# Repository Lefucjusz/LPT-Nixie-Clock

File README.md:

# LPT-Nixie-Clock
DOS-controlled Nixie clock, built with four IN-1/LC-516 tubes and interfaced through the LPT port.

<figure>
    
    <figcaption><i>Photo of a complete project (LC-516 tubes)</i></figcaption>
</figure>

## Features
* Supports IN-1 and LC-516 Nixie tubes
* Multiplexed display with four digits and a colon
* Onboard high-voltage boost converter; requires only a single 12V power supply
* Serial control interface using just three control wires
* Hardware designed exclusively with easily available components
* Control software implemented as a DOS TSR written in TASM
* Uses the AT-style RTC programming model as the time source and multiplexing timebase
* Connection via the PC’s LPT port

## Motivation
This project is another attempt to answer a question I’ve been asking myself ever since I built the [Xi8088](https://github.com/skiselev/xi_8088):

*What can I use this PC for that it was never really designed to do, yet is still possible, reasonably practical, and fun to work on?*

My first attempt was a WAV player - [WAVWSS](https://github.com/Lefucjusz/WAVWSS). With that working, I started looking for another challenge, Nixie clock felt like a perfect next step:

* it smoothly merges insanity with practicality: it is a Nixie clock - a useful and visually appealing device - controlled by genuinely ancient hardware that
was never intended for such a task, especially not via a printer port;
* while not fully period-correct, the combination of a PC/XT-class computer built largely from 74xx TTL logic and Nixie tubes has a strong appeal for a low-level
tinkerer like me :smile:;
* it provided a good opportunity to learn long-forgotten skills such as writing DOS TSRs, particularly in assembly language, the task I had never tried before.
The project is programmatically simple, making debugging relatively straightforward when things went wrong;
* it allowed me to validate the idea of a Nixie tube driver circuit built entirely from easily available components, avoiding long-discontinued parts such as
SN74141 or its Soviet counterpart K155ID1, which are increasingly expensive and slowly becoming unobtainium;
* finally, it gave me the motivation to put to use a set of IN-1 Nixie tubes I bought around 2020, but had never used due to their large, hard to use sockets.

## Hardware

> [!CAUTION]
> This project involves high voltages! Although the external power supply is only 12V, voltages of around 200V are present on the PCB and components during normal
operation. Even higher voltages may occur if the boost converter feedback loop malfunctions, for example due to incorrect PCB assembly. **Such voltages can be lethal.**
The author takes no responsibility for any damage, injury, or loss resulting from the use or construction of this project. Build and operate it entirely at your own risk.

> [!WARNING]
> Use of this project may pose a risk to your vintage hardware. The author accepts no responsibility for any resulting damage.
 
### Schematic and PCB layout

[Schematic](https://github.com/Lefucjusz/LPT-Nixie-Clock/blob/master/kicad/lpt_nixie_clock_schematic_color.pdf)

[PCB layout](https://github.com/Lefucjusz/LPT-Nixie-Clock/blob/master/kicad/lpt_nixie_clock_board_color.pdf)

### Principle of operation

#### Logic design and display interface
The logic section, which forms the input interface for the display, consists of U3 (4028), U6 (74HC595), and U7 (74HCT74). U6 together with U7 forms a 9-bit
SIPO register with an output latch. The register outputs are connected to:
* the anode drivers for the Nixie tubes;
* the colon cathode driver;
* the BCD-to-decimal decoder (U3), which controls the Nixie cathode drivers.

The display operates in a multiplexed fashion: all corresponding Nixie digits share connections, and only one tube is turned on at a time. Rapidly switching between
tubes (every 1/64 millisecond in this project) creates the illusion that all tubes are lit simultaneously. This approach drastically reduces the number of required shift
register outputs or control lines compared to static (individual) tube control.

The display control word is loaded serially using three lines: `DATA`, `CLOCK`, and `LATCH`. The loading occurs in two steps:
1. The control word is shifted into the register using the `DATA` and `CLOCK` lines.
2. After the word is fully loaded, a rising edge on the LATCH line updates the output register.

The exact timing diagram, along with a description of each control word bit, is shown below.

* `A1..4` - logic high enables the anode driver, A1 is the leftmost tube
* `1..8` - BCD value of a digit to be displayed
* `:` - logic high turns on the colon 

Some design choices may seem unusual at first. Initially, I did not use the 4028 decoder for the cathode control signals. Instead, the inputs of the Nixie cathode drivers
were connected directly to the outputs of two cascaded 74HC595 shift registers. The problem with this approach was efficiency: sending 15 bits
(10 cathodes, 4 anodes, colon) to a shift register is more costly than sending just 9 bits. Each bit requires 3 OUT instructions:
1. set `DATA` line state,
2. set `CLOCK` line high,
3. set `CLOCK` line low.

Each control word also requires a `LATCH` toggle to update output register: 2 additional OUT instructions.

At a 256Hz multiplexing rate, using a 15-bit register results in:

```
256 * ((15 * 3) + 2) = 12032 OUT instructions per second
```

Tests on a breadboard prototype showed that spamming the LPT port with this many instructions from within an ISR was beyond the capabilities of an 8088 at 4.77MHz.
Even at 8MHz, the PC was noticeably slowed - for example, WAV playback using WAVWSS would stutter while the clock was running.

Switching to a 9-bit register reduces the required instructions to:

```
256 * ((9 * 3) + 2) = 7424 OUT instructions per second
```

Still significant, but much more manageable.

With a 9-bit register, only one bit of a second, cascaded 74HC595 was actually needed. Rather than using an entire additional shift register just for a single bit,
I replaced it with a 74HCT74 flip-flop, which met the circuit requirements much better. I also happened to have plenty of 74x74 chips and only a few 74HC595s, so this
choice made it easy to make good use of the components I already had on hand.

#### Anode drivers
For the anode drivers, I usually go with the classic solution of a two-transistor high-side switch, which allows controlling high voltages using standard logic levels.

<figure>
    
    <figcaption><i>Two-transistor high side switch</i></figcaption>
</figure>

<br/>
<br/>

This time, however, I decided to experiment with an approach using optocouplers. I had seen similar solutions in other projects, but they typically used TLP627
optocouplers or alternatives with a similarly high collector-emitter breakdown voltage `VCEO ≈ 300V`. They are much harder to source than common, widely
available types.

I wondered whether such a high breakdown voltage was really necessary. After some consideration, I thought that as long as the following condition is met, the
circuit should operate correctly:

```
Va < Vm + VCEO

where: 
Va - anode voltage from boost converter
Vm - maintaining voltage of a Nixie tube
VCEO - collector-emitter breakdown voltage of an optocoupler’s transistor
```

Looking through my components, I found a few CNY17-3 optocouplers with `VCEO = 70V` and decided to test them in a prototype circuit. They worked, and also reduced
the component count compared to the traditional 2-transistor driver, so I decided to keep this solution.

#### Cathode drivers

Using the same reasoning as for the anode driver, I decided to experiment with ULN2004 chips for the Nixie cathode drivers. These have a VCEO of only 50V, so
this solution is definitely not very robust and is far from production-ready. The drivers operate close to or even slightly above their absolute maximum ratings.

During several months of testing, I didn’t blow a single ULN2004 channel, so either I was very lucky or happened to have particularly sturdy chips. However, the
ULN2004-based solution does cause an issue when driving the neon bulbs used for the colon; see [Known Issues](#known-issues).

> [!WARNING]
> If anyone comes across this project and wants to take inspiration from it, please avoid this approach in your own projects! Operating so close to the maximum 
ratings of components is an engineering antipattern that should be avoided whenever possible, even in non-critical applications.

#### Boost converter

The boost converter circuit is a classic NE555-based circuit, using the chip in a somewhat unconventional way. This design has a number of drawbacks: low efficiency,
feedback that affects not only the duty cycle but also the switching frequency, poor voltage stability under varying load, significant temperature drift due to the
reference being based on forward voltage of feedback transistor's B-E junction, etc.

Despite these limitations, I chose this approach for one main reason: it is simple and relies only on widely available components.

### Assembly

> [!WARNING]
> Nixie tubes and neon bulbs are mounted on the opposite side of the PCB from the rest of the components.

#### PCB - top side

The top side of the PCB contains all components except the Nixie tubes and neon bulbs. When assembling this layer, install the components from the smallest to the largest -
this makes the process much easier.

Pay close attention to the polarity of diodes and electrolytic capacitors, and ensure all ICs are installed with the correct orientation - `U4` and `U5` are oriented differently
from the rest. I strongly recommend using sockets for all ICs. I use them in all of my projects: they are inexpensive and can save a lot of soldering work if any IC ever
needs to be replaced.

#### PCB - bottom side
The bottom side of the PCB is where the Nixie tubes and neon bulbs are mounted. Start by installing the Nixie tubes. They can be either soldered directly to the PCB or
socketed. Both approaches have their advantages and drawbacks:
* direct soldering is quicker, but replacing a tube later will be difficult and will require desoldering;
* socketing makes tube replacement easy, but is more involved during assembly.

If you decide to solder the tubes directly, there is not much to watch out for - the tube base is keyed, so simply align it correctly, insert it into the PCB, and solder.

If you decide to use sockets, the process is a bit more complicated. Unfortunately, Nixie tube sockets were never standardized and are no longer manufactured, so they are
not available as off-the-shelf parts. For this design, I used female contacts intended for 5.08mm Molex-type CD/HDD power plugs. These are widely available and likely to
remain so for the foreseeable future.

However, these contacts cannot be used as-is - they require slight modification to fit the circular pads on the PCB. This is the most tedious part of the socketing process:
1. Remove the cable crimp section of the contact by cutting or breaking it off. Its irregular shape prevents the contact from fitting properly into the circular PCB pad.
2. Check the fit in the PCB pad. Some contacts have a slightly oversized diameter. If a contact does not fit easily, gently squeeze the soldering end with pliers to reduce
the diameter.

<figure>
    
    <figcaption><i>Molex contact with cable crimp section removed</i></figcaption>
</figure>

<br/>
<br/>

Perform these two steps on all contacts before proceeding, so that they are ready for installation.

Once all contacts are modified, install the first set onto the pins of a Nixie tube. Installing the contacts on the tube first and inserting the assembly as a whole makes
it much easier to keep the contacts properly aligned. After the entire set of contacts is placed on the tube, align it with the PCB footprint using the base key, then
carefully insert all contacts into their respective pads. This step requires some patience; tweezers are very helpful here.

Once all pins are fully inserted - ideally up to the retention springs - solder the contacts, remove the tube, and repeat the entire process for the remaining three Nixie tubes.

After all the contacts have been soldered, install the neon bulbs, then insert Nixie tubes into the sockets.

#### PCB - cleaning and final inspection

When the assembly is completed, clean the PCB thoroughly using isopropyl alcohol to remove any residual flux. Perform a careful final inspection: check for bad solder joints,
accidental solder bridges or any potential shorts. Make sure all ICs are correctly oriented and look for any obvious mistakes before powering up the board.

<figure>
    
    <figcaption><i>Fully assembled PCB - top view</i></figcaption>
</figure>

#### LPT cable

To connect the device to the PC, an LPT-to-board connector cable is required. The wiring diagram is shown below.

| DB-25 LPT pin    | PCB connector pin | Signal name |
|------------------|-------------------|-------------|
| 2                | 4                 | DATA        |
| 3                | 3                 | CLOCK       |
| 4                | 2                 | LATCH       |
| 18-25 (pick one) | 1                 | GND         |

On the PC side, a standard male DB-25 connector is used. On the board side, any 4-pin connector with a 2.54 mm pitch that fits the available space can be used. In my build, 
I chose a Molex KK-254 series connector, mainly because I already had suitable parts left over from another project. The connector may also be omitted entirely, with the cable 
soldered directly to the PCB.

The cable itself must contain at least four conductors. I used a generic Cat 5e Ethernet cable, taking one wire from each twisted pair for the signal and connecting the 
corresponding paired wire to ground. This arrangement helps reduce noise pickup on the control lines.

### Bring-up

After the PCB is assembled and cleaned, the device is ready to be powered up for the first time. If the board was assembled correctly, it should work without issues. During 
the initial power-up, the Nixie tube anode voltage must be set to 170V. This adjustment is performed only once.

> [!CAUTION]
> Reminder: high voltages (up to approx. 200V) are present on the PCB during this procedure. Neither the board nor any components should be touched while the device
is powered. Capacitor C4 may remain charged for several minutes after the power supply has been turned off. Do not touch the board or components immediately after
power-down; always verify that the high-voltage rail has discharged before handling the PCB.

1. Set the `RV1` potentiometer (labeled `170V Adj.`) to approximately its mid-position. This provides a safe starting point and helps ensure that the output voltage
will not exceed the target value.
2. Connect a voltmeter with a range of at least 200V to the `TP1` test point.
3. Connect a 9-12V power supply with a current rating of at least 0.5A to the `J1` connector, observing correct polarity. The circuit includes reverse-polarity
protection, but it will not operate if the supply is connected backwards. If available, a bench power supply with adjustable current limiting is strongly recommended. 
Set the current limit to 0.5A.
4. Do not connect the control cable at this stage.
5. Turn on the power supply. Some digits may begin to glow faintly - this is normal. Upon power-up, the output states of the SIPO register are undefined. Due to
limitations of the 74HC595 reset mechanism (it clears only the shift register, not the output register), implementing a power-on reset circuit that guarantees all
tubes are off would significantly increase circuit complexity. Since the display is not intended to operate without control signals, I've decided that this behavior
is acceptable.
6. Adjust `RV1` until the voltage at `TP1` reads 170V ±2V. Turning the potentiometer clockwise increases the voltage; turning it counterclockwise decreases it.
**If the voltage at `TP1` exceeds 250V and cannot be reduced using `RV1`, immediately turn off the power supply and verify the assembly of the boost converter's
feedback loop. Continued operation at this voltage may cause `C4` to fail catastrophically.**
7. Turn off the power supply.
8. Connect the control cable between the LPT port and the board.
9. Start the DOS TSR.
10. Turn the power supply back on. If the board and the cable were assembled correctly, the display should show the current RTC time, and the colon should blink once per second.

### Known issues

#### Colon not turning off completely
This issue is caused by the low VCEO rating of the ULN2004. Neon bulbs have a much lower maintaining voltage than Nixie tubes and as a result, the condition
described in the [Anode Drivers](#anode-drivers) is not met. This causes the ULN2004 output transistor to enter C-E breakdown. Although the transistor is not
damaged due to the limited current, it continues to conduct even when its base is not being driven.

I didn't notice this problem during prototyping stage, as the neon bulbs I initially used happened to work correctly under these conditions. They likely have 
an unusually high maintaining voltage.

This issue can be worked around in two ways:

1. **Add a parallel resistor across each neon bulb.** Solder the resistor directly to the pads of each bulb. A value of 470kΩ works well in most cases. This forms
a resistor divider with the neon bulb’s  current-limiting resistor and lowers the voltage across the bulb below its maintaining voltage, even while the driver
transistor is in breakdown.
2. **Lower the anode voltage** using `RV1` until both neon bulbs fully extinguish when turned off. This will also reduce the brightness of Nixie tubes, though.

#### Too large footprint for non-polar capacitors
Somehow, I ended up selecting a footprint with a 7.5mm pin pitch instead of 5mm, and didn’t notice it despite reviewing the project countless times before placing an
order for PCBs. As a result, typical 100nF ceramic disc capacitors are too narrow for the footprint, and their leads need to be bent to fit. I’ll likely fix this if
I ever order another batch of PCBs, and (assuming the corrected version works as expected) I’ll update the design files.

### Bill of Materials
| Component type | Reference          | Description                                 | Quantity | Possible sources and notes                                          |
|----------------|--------------------|---------------------------------------------|----------|---------------------------------------------------------------------|
| PCB            | -                  | LPT Nixie Clock PCB                         | 1        | Your favourite PCB manufacturer                                     |
| Capacitor      | C1, C6, C7, C9-C11 | 100nF ceramic                               | 6        | TME CC-100N                                                         |
| Capacitor      | C2                 | 2.2nF ceramic or polyester                  | 1        | TME R82EC1220DQ50J                                                  |
| Capacitor      | C3                 | 47pF 1kV ceramic                            | 1        | TME CCH-47P/1000V                                                   |
| Capacitor      | C4                 | 4.7μF 250V electrolytic                     | 1        | TME PF2E4R7MNN0812                                                  |
| Capacitor      | C5                 | 330μF electrolytic                          | 1        | TME PF1C331MNN0812                                                  |
| Capacitor      | C8                 | 10μF electrolytic                           | 1        | TME CE-10/50PHT-Y                                                   |
| Resistor       | R1                 | 56kΩ                                        | 1        | TME MBB02070C5602FCT00                                              |
| Resistor       | R2                 | 1kΩ                                         | 1        | TME MRS25000C1001FCT00                                              |
| Resistor       | R3                 | 10kΩ                                        | 1        | TME MRS25000C1002FCT00                                              |
| Resistor       | R4                 | 2.2kΩ                                       | 1        | TME MRS25000C2201FCT00                                              |
| Resistor       | R5                 | 330kΩ                                       | 1        | TME MBB02070C3303FCT00                                              |
| Resistor       | R6                 | 820Ω                                        | 1        | TME MBB02070C8200FCT00                                              |
| Resistor       | R7, R9, R13, R15   | 470Ω                                        | 4        | TME MF006JJ0471A50                                                  |
| Resistor       | R8, R10, R14, R16  | 6.8kΩ                                       | 4        | TME MFFU2FF6801A50                                                  |
| Resistor       | R11, R12           | 180kΩ                                       | 2        | TME MRS25000C1803FCT00                                              |
| Resistor       | R17                | 0Ω                                          | 1        | Note: used only in prototype, install a jumper                      |
| Trimpot        | RV1                | 2.2kΩ                                       | 1        | TME CA6V-2K2                                                        |
| Diode          | D1                 | UF4007                                      | 1        | TME UF4007-DC                                                       |
| Diode          | D2                 | 1N5817                                      | 1        | TME 1N5817-ST                                                       |
| Inductor       | L1                 | 100μH 1A                                    | 1        | TME RLB0914-101KL                                                   |
| Transistor     | Q1                 | BC547C                                      | 1        | TME BC547C-DIO                                                      |
| Transistor     | Q2                 | IRF740                                      | 1        | TME IRF740PBF-BE3                                                   |
| Optocoupler    | OK1-OK4            | CNY17-3                                     | 4        | TME CNY17-3X                                                        |
| IC             | U1                 | NE555                                       | 1        | TME NE555P                                                          |
| IC             | U2                 | 78L05                                       | 1        | TME AS78L05Z-E1                                                     |
| IC             | U3                 | 4028                                        | 1        | TME CD4028BE                                                        |
| IC             | U4, U5             | ULN2004A                                    | 2        | TME ULN2004A                                                        |
| IC             | U6                 | 74HC595                                     | 1        | TME 74HC595N-TT                                                     |
| IC             | U7                 | 74HCT74                                     | 1        | TME SN74HCT74N                                                      |
| IC socket      | U1                 | 8-pin 300mil DIP socket                     | 1        | TME 1-2199298-2; Note: optional                                     |
| IC socket      | U3-U6              | 16-pin 300mil DIP socket                    | 4        | TME ICVT-16P; Note: optional                                        |
| IC socket      | U7                 | 14-pin 300mil DIP socket                    | 1        | TME ICVT-14P; Note: optional                                        |
| Fuse           | F1                 | 500mA 250VAC 5x20mm slow-blow fuse          | 1        | TME UDA500MA250V                                                    |
| Fuse socket    | F1                 | Fuse mounting contact                       | 2        | TME ZH8                                                             |
| Connector      | J1                 | 2-pin 5mm 90° screw terminal block          | 1        | TME DG301-5.0-2P12                                                  |
| Connector      | J2                 | Molex KK-254 4-pin PCB connector            | 1        | TME MX-6410-04A                                                     |
| Neon bulb      | NE1, NE2           | Neon bulb w/o resistor                      | 2        | TME NEON-2                                                          |
| Nixie tube     | V1-V4              | IN-1 or LC-516                              | 4        | eBay, Allegro etc.                                                  |
| Contact        | V1-V4              | CD/HDD 5.08mm female power plug contact     | 44       | TME DFC01DR; Note: 11 pcs. for each tube; optional, but recommended |
| Plug           | -                  | DB-25 male plug for cable                   | 1        | TME DSC-025; Note: for signal cable                                 |
| Plug enclosure | -                  | DB-25 plug enclosure                        | 1        | TME DSC-225; Note: for signal cable                                 |
| Plug           | -                  | Molex KK-254 4-pin cable connector          | 1        | TME MX-47054-1000; Note: for signal cable                           |
| Contact        | -                  | Molex KK-254 contact                        | 4        | TME MX-4809C-P914L; Note: for signal cable                          |
| Cable          | -                  | Any signal cable with at least 4 conductors | 1        | Note: for signal cable                                              |
| Power supply   | -                  | 9-12VDC 0.5A power supply                   | 1        | TME POSC12100A-25                                                   |

## Software
The program was developed on the Xi8088 using Borland Turbo Assembler 2.01. Initially, I considered implementing it in C, as this is my mother tongue in programming :smile:.
However, I decided it would be more interesting to go fully low-level, try 8088 assembly, and minimize the size of the TSR as much as possible.

To keep the design simple, I did not implement any unloading or presence-checking mechanisms. I also didn't explore loading the program into upper memory. My Xi8088 build has
only 640KB of RAM, so I neither had a practical need for this nor a convenient way to test it. The final TSR occupies 720B of conventional memory.

<figure>
    
    <figcaption><i>TSR memory usage</i></figcaption>
</figure>

### Principle of operation
At a high level, the program’s functionality is straightforward. Upon startup, it installs an interrupt handler for the RTC interrupt, configures the RTC interrupts and
terminates. From that point on, the RTC periodically invokes the installed handler, which is responsible for updating the display.

Internally, the program follows a fairly standard DOS TSR architecture and can be logically divided into an initialization part and a resident part. The initialization part runs
when the program is executed and is responsible for the following tasks:
* installing an interrupt handler for INT 70h (IRQ 8, connected to the RTC interrupt line), which effectively drives the entire resident part of the program;
* configuring the RTC periodic interrupt rate to 256Hz, which is used as the display multiplexing timebase;
* enabling the RTC update-ended interrupt, used to update the colon state and time variables;
* unmasking IRQ 8 in the 8259 PIC;
* terminating the program in a way that leaves the resident portion in memory.

The resident part is the core of the program. Each time the RTC asserts an interrupt request, the installed ISR is invoked and executes the following steps:
* all registers clobbered by the ISR are pushed onto the stack;
* the RTC interrupt flags are read to determine the interrupt source;
* if a periodic interrupt is pending, the display update procedure is executed; this procedure keeps track of the currently active Nixie tube to perform multiplexing, converts
the time variables into the serial control word format, transmits the data frame via the LPT port, and executes the cathode depoisoning algorithm (described below);
* if an update-ended interrupt is pending, the time update procedure is called; this procedure keeps the time variables and colon state synchronized with the RTC;
* finally, IRQ 8 is acknowledged in the 8259 PICs, register values are restored from the stack, and the ISR returns.

#### Cathode depoisoning algorithm
The purpose of this algorithm is to prevent (or at least reduce) a well-known phenomenon inherent to Nixie tube technology. When a cathode (digit) is active, material from
that cathode is sputtered onto the glass envelope and onto the inactive cathodes. If certain digits remain unused for long periods while others are displayed frequently, the
deposited material can become thick enough to disturb the current flow, causing so-called cathode poisoning. A poisoned cathode may glow very weakly, develop dark spots or
stop glowing altogether. Some excellent photographs illustrating this phenomenon can be found on [Dieter's Nixie World page](https://www.tube-tester.com/sites/nixie/different/cathode%20poisoning/cathode-poisoning.htm).

Some Nixie tubes are more prone to this than others, but over time the effect can show up in almost any tube if it is not actively prevented.

To counter this, a simple cathode “depoisoning” algorithm is implemented in the TSR. Once per hour, the algorithm cycles through all digits on all tubes, ensuring that every
cathode is periodically activated. This is a standard approach and one I have used in my Nixie-related projects from the beginning. It has proven very effective for IN-12 and
LC-531 tubes. I haven't had a long-term experience with IN-1 tubes yet, but I expect it to work just as well - time will tell :smile:.

<figure>
  
  <figcaption><i>Depoisoning algorithm at work (IN-1 tubes)</i></figcaption>
</figure>

### Compatibility
The software has not been tested on a wide range of machines, but it should work on any system with:
* an LPT port located at I/O address 378h and,
* an AT-style RTC using the MC146818P / DS1287 programming model.

In addition to the Xi8088 used for development, the program has been tested on a 386-class PC, where it worked without issues.

In principle, the software could be adapted to systems without such an RTC. The display update routine needs to be invoked at a rate of at least 250Hz to maintain smooth
multiplexing and an alternative time source would need to be provided.

The TSR uses the RTC interrupt exclusively; the original ISR previously installed on the RTC vector is replaced rather than chained. This is probably not the wisest design choice,
but as far as I am aware, DOS itself doesn't use this interrupt for any purpose. Problems may arise if other software expects to receive RTC interrupts.
Unfortunately, I don't know which programs might rely on this, as my retrocomputing experience is still fairly limited.

### Compiling
Assuming Borland Turbo Assembler 2.01 is installed and added to system PATH, the program can be assembled as follows.

1. Assemble the source file `CLOCK.ASM` using `TASM`:
```
tasm clock.asm
```
This will produce the object file `CLOCK.OBJ`.

2. Link the object file using `TLINK`:
```
tlink /t clock.obj
```
The `/t` switch tells the linker to use the tiny memory model and generate a `.COM` file instead of an `.EXE`.

If both commands run without errors, the output `CLOCK.COM` file will be created and is ready to run.

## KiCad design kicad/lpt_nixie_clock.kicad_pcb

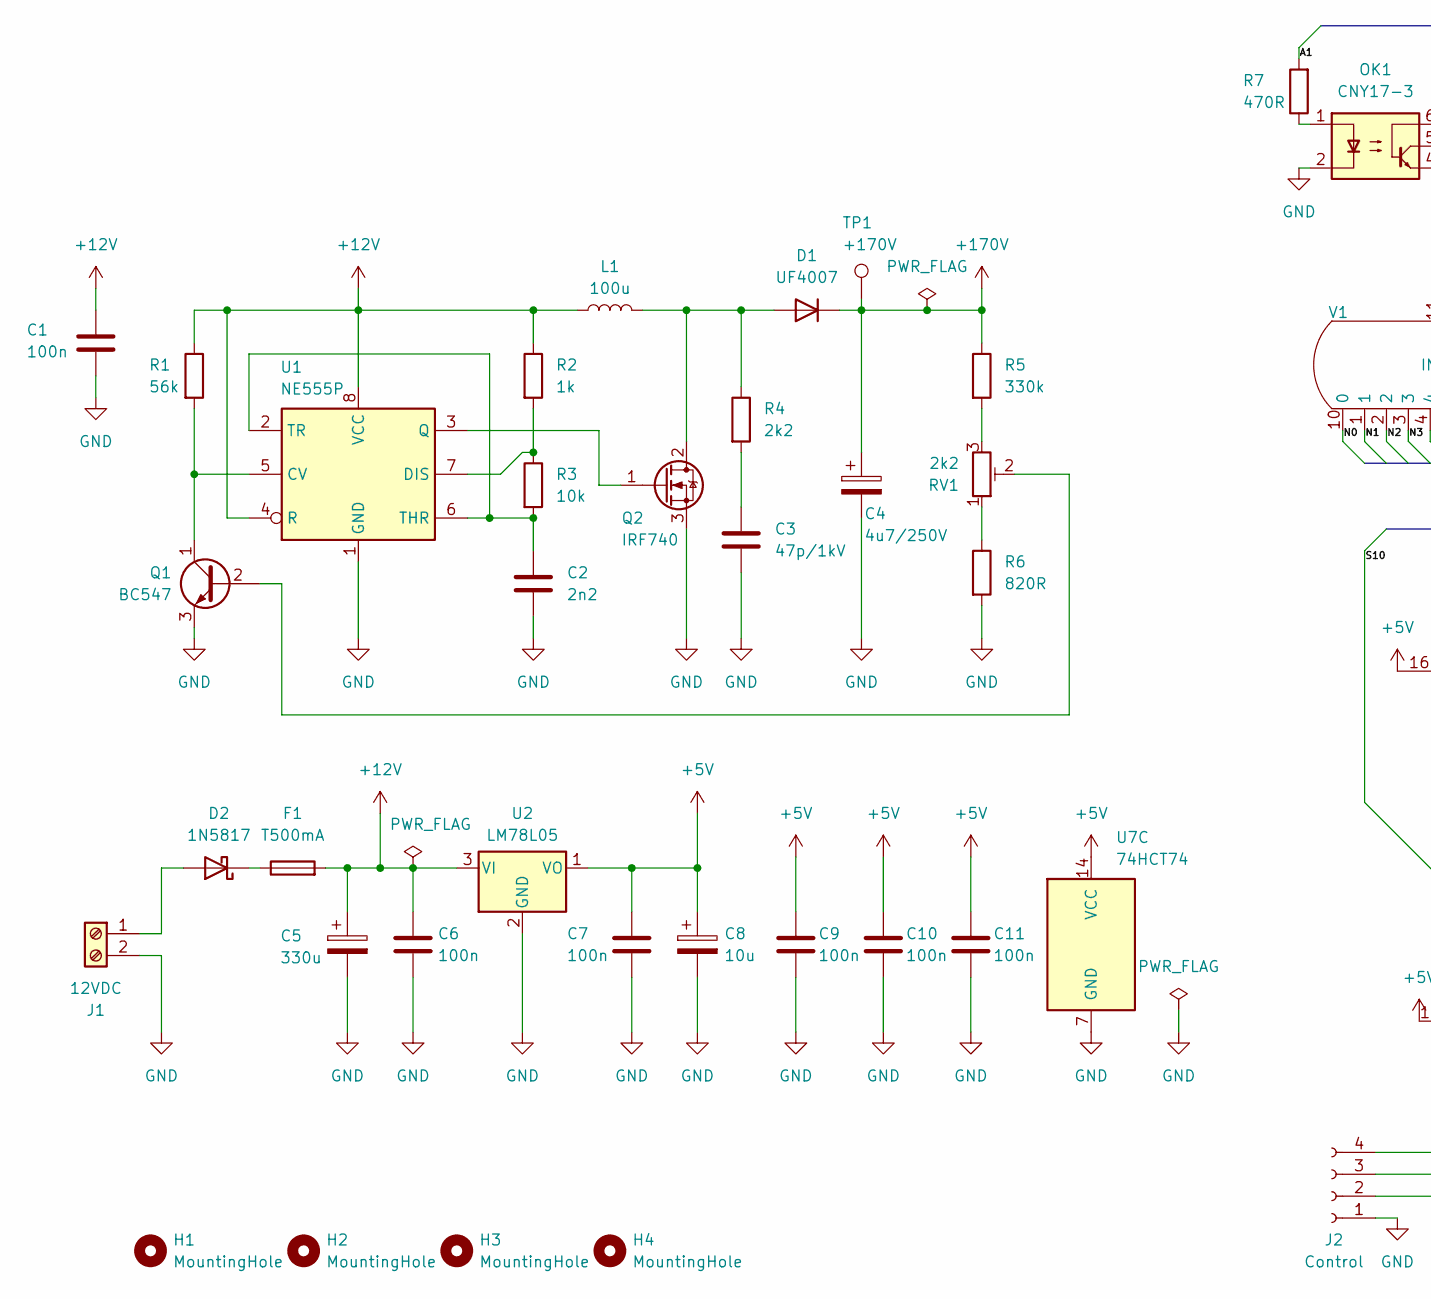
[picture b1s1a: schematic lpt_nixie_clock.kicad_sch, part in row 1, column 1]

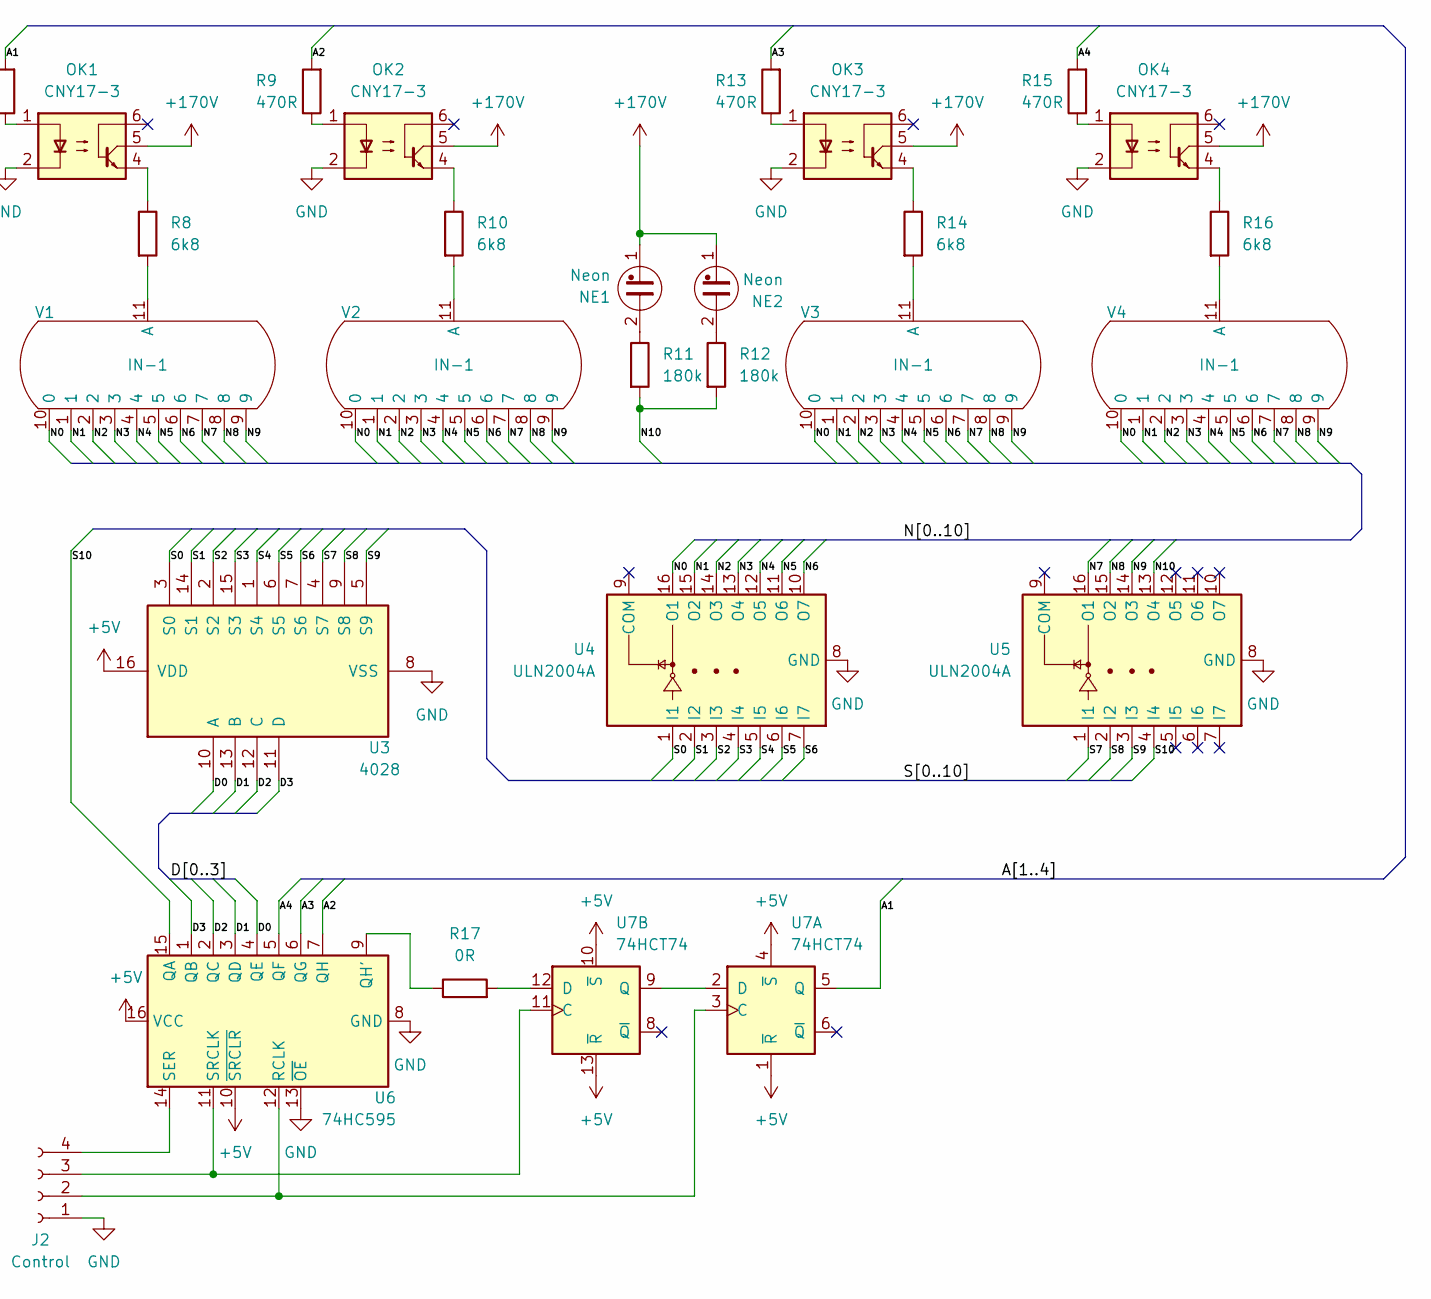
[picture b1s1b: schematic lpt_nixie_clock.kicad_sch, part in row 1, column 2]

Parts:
C1, C6, C7, C9, C10, C11: 100n; C_Axial_L3.8mm_D2.6mm_P7.50mm_Horizontal
C2: 2n2; C_Axial_L3.8mm_D2.6mm_P7.50mm_Horizontal
C3: 47p/1kV; C_Axial_L3.8mm_D2.6mm_P7.50mm_Horizontal
C4: 4u7/250V; CP_Radial_D8.0mm_P3.50mm
C5: 330u; CP_Radial_D6.3mm_P2.50mm
C8: 10u; CP_Radial_D5.0mm_P2.00mm
D1: UF4007; D_DO-41_SOD81_P10.16mm_Horizontal
D2: 1N5817; D_DO-41_SOD81_P10.16mm_Horizontal
F1: T500mA; Fuseholder_Clip-5x20mm_Littelfuse_520_Inline_P20.50x5.80mm_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
H1, H2, H3, H4: MountingHole; MountingHole_3.2mm_M3
J1: 12VDC; TerminalBlock_MaiXu_MX126-5.0-02P_1x02_P5.00mm
J2: Control; Molex_KK-254_AE-6410-04A_1x04_P2.54mm_Vertical
L1: 100u; L_Radial_D9.5mm_P5.00mm_Fastron_07HVP
NE1, NE2: Neon; LED_D5.0mm
OK1, OK2, OK3, OK4: CNY17-3; DIP-6_W7.62mm_LongPads
Q1: BC547; TO-92_HandSolder
Q2: IRF740; TO-220-3_Vertical
R1: 56k; R_Axial_DIN0207_L6.3mm_D2.5mm_P10.16mm_Horizontal
R2: 1k; R_Axial_DIN0207_L6.3mm_D2.5mm_P10.16mm_Horizontal
R3: 10k; R_Axial_DIN0207_L6.3mm_D2.5mm_P10.16mm_Horizontal
R4: 2k2; R_Axial_DIN0207_L6.3mm_D2.5mm_P10.16mm_Horizontal
R5: 330k; R_Axial_DIN0207_L6.3mm_D2.5mm_P10.16mm_Horizontal
R6: 820R; R_Axial_DIN0207_L6.3mm_D2.5mm_P10.16mm_Horizontal
R7, R9, R13, R15: 470R; R_Axial_DIN0207_L6.3mm_D2.5mm_P10.16mm_Horizontal
R8, R10, R14, R16: 6k8; R_Axial_DIN0207_L6.3mm_D2.5mm_P10.16mm_Horizontal
R11, R12: 180k; R_Axial_DIN0207_L6.3mm_D2.5mm_P10.16mm_Horizontal
R17: 0R; R_Axial_DIN0207_L6.3mm_D2.5mm_P10.16mm_Horizontal
RV1: 2k2; Potentiometer_Runtron_RM-065_Vertical
TP1: +170V; Pin_D1.0mm_L10.0mm
U1: NE555P; DIP-8_W7.62mm_LongPads
U2: LM78L05; TO-92_HandSolder
U3: 4028; DIP-16_W7.62mm_LongPads
U4, U5: ULN2004A; DIP-16_W7.62mm_LongPads
U6: 74HC595; DIP-16_W7.62mm_LongPads
U7: 74HCT74; DIP-14_W7.62mm_LongPads
V1, V2, V3, V4: IN-1

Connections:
+5V: C7.1, C8.1, C9.1, C10.1, C11.1, U2.1 (VO), U3.16 (VDD), U6.10 (~SRCLR), U6.16 (VCC), U7.1 (~R), U7.4 (~S), U7.10 (~S), U7.13 (~R), U7.14 (VCC)
+12V: C1.1, C5.1, C6.1, F1.2, L1.1, R1.1, R2.1, U1.4 (R), U1.8 (VCC), U2.3 (VI)
+170V: C4.1, D1.1 (K), NE1.1, NE2.1, OK1.5, OK2.5, OK3.5, OK4.5, R5.1, TP1.1
/A1: R7.2, U7.5 (Q)
/A2: R9.2, U6.7 (QH)
/A3: R13.2, U6.6 (QG)
/A4: R15.2, U6.5 (QF)
/D0: U3.10 (A), U6.4 (QE)
/D1: U3.13 (B), U6.3 (QD)
/D2: U3.12 (C), U6.2 (QC)
/D3: U3.11 (D), U6.1 (QB)
/N0: U4.16 (O1), V1.10 (0), V2.10 (0), V3.10 (0), V4.10 (0)
/N1: U4.15 (O2), V1.1, V2.1, V3.1, V4.1
/N2: U4.14 (O3), V1.2, V2.2, V3.2, V4.2
/N3: U4.13 (O4), V1.3, V2.3, V3.3, V4.3
/N4: U4.12 (O5), V1.4, V2.4, V3.4, V4.4
/N5: U4.11 (O6), V1.5, V2.5, V3.5, V4.5
/N6: U4.10 (O7), V1.6, V2.6, V3.6, V4.6
/N7: U5.16 (O1), V1.7, V2.7, V3.7, V4.7
/N8: U5.15 (O2), V1.8, V2.8, V3.8, V4.8
/N9: U5.14 (O3), V1.9, V2.9, V3.9, V4.9
/N10: R11.2, R12.2, U5.13 (O4)
/S0: U3.3 (S0), U4.1 (I1)
/S1: U3.14 (S1), U4.2 (I2)
/S2: U3.2 (S2), U4.3 (I3)
/S3: U3.15 (S3), U4.4 (I4)
/S4: U3.1 (S4), U4.5 (I5)
/S5: U3.6 (S5), U4.6 (I6)
/S6: U3.7 (S6), U4.7 (I7)
/S7: U3.4 (S7), U5.1 (I1)
/S8: U3.9 (S8), U5.2 (I2)
/S9: U3.5 (S9), U5.3 (I3)
/S10: U5.4 (I4), U6.15 (QA)
GND: C1.2, C2.2, C3.2, C4.2, C5.2, C6.2, C7.2, C8.2, C9.2, C10.2, C11.2, J1.2, J2.1, OK1.2, OK2.2, OK3.2, OK4.2, Q1.3 (E), Q2.3 (S), R6.2, U1.1 (GND), U2.2 (GND), U3.8 (VSS), U4.8 (GND), U5.8 (GND), U6.8 (GND), U6.13 (~OE), U7.7 (GND)
unnamed: C3.1, R4.2
unnamed: D1.2 (A), L1.2, Q2.2 (D), R4.1
unnamed: D2.2 (A), J1.1
unnamed: D2.1 (K), F1.1
unnamed: J2.2, U6.12 (RCLK), U7.3 (C)
unnamed: J2.3, U6.11 (SRCLK), U7.11 (C)
unnamed: J2.4, U6.14 (SER)
unnamed: NE1.2, R11.1
unnamed: NE2.2, R12.1
unnamed: OK1.1, R7.1
unnamed: OK1.4, R8.1
unnamed: OK2.1, R9.1
unnamed: OK2.4, R10.1
unnamed: OK3.1, R13.1
unnamed: OK3.4, R14.1
unnamed: OK4.1, R15.1
unnamed: OK4.4, R16.1
unnamed: Q1.2 (B), RV1.2
unnamed: Q1.1 (C), R1.2, U1.5 (CV)
unnamed: Q2.1 (G), U1.3 (Q)
unnamed: R5.2, RV1.3
unnamed: R6.1, RV1.1
unnamed: R2.2, R3.1, U1.7 (DIS)
unnamed: C2.1, R3.2, U1.2 (TR), U1.6 (THR)
unnamed: R17.1, U6.9 (QH')
unnamed: U7.2 (D), U7.9 (Q)
unnamed: R17.2, U7.12 (D)
unnamed: R8.2, V1.11 (A)
unnamed: R10.2, V2.11 (A)
unnamed: R14.2, V3.11 (A)
unnamed: R16.2, V4.11 (A)

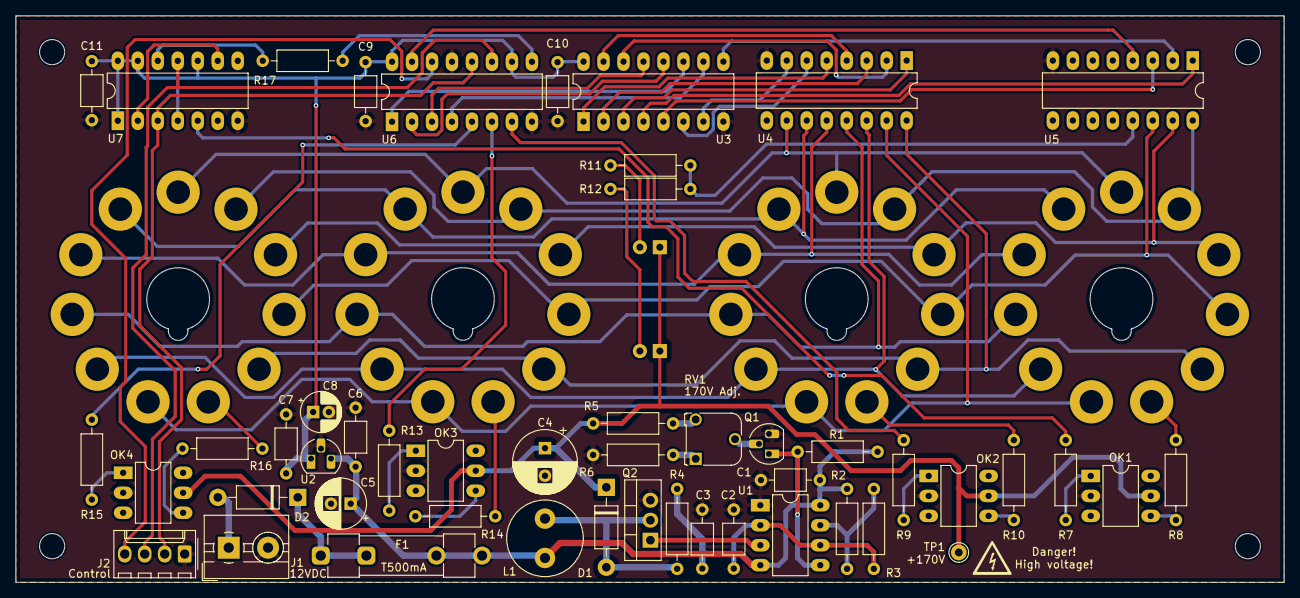
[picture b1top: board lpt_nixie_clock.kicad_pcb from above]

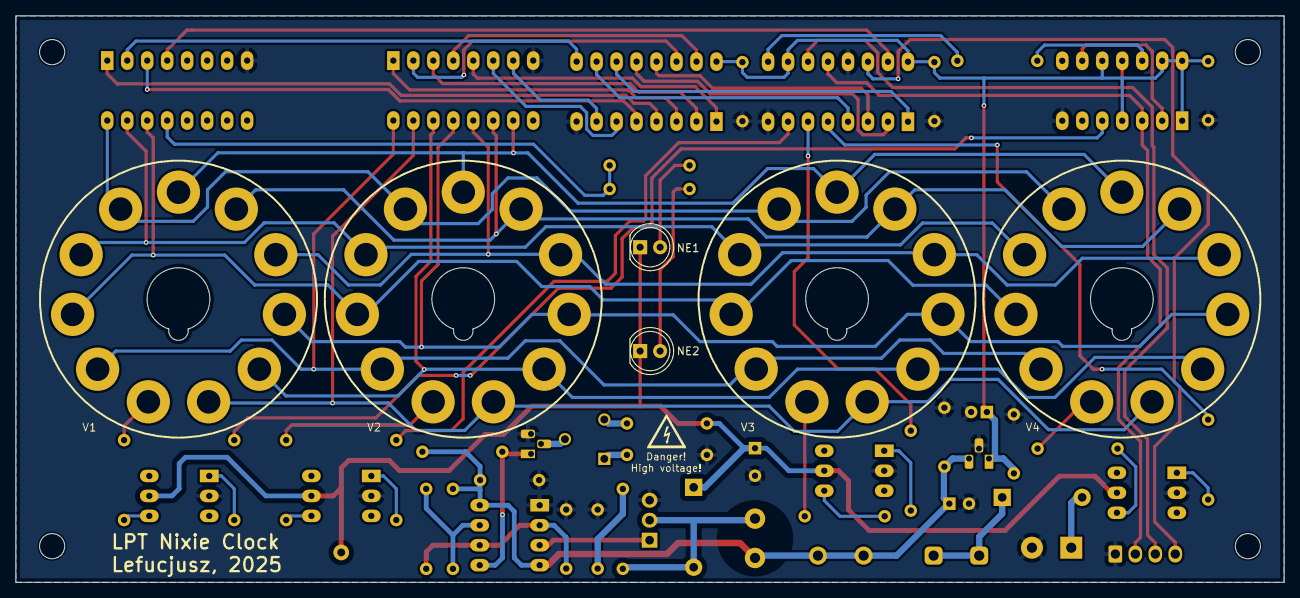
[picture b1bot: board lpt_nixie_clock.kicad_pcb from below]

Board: 2 copper layers, 161.2 x 72.0 mm, 59 parts (6 on the bottom side), 65 nets.

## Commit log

2026-01-06 Add KiCad design files and assembly source
    * Added KiCad design files.
    * Added Gerbers rendered for JLCPCB.
    * Added TSR assembly source
2026-01-07 Add first README version
    Added first README version with almost complete
    description of a hardware part.
2026-01-10 Add next part of README
    * Added two missing sections to the README:
    'PCB assembly' and 'Bring-up'.
    * Minor fixes throughout the README.
2026-01-10 Add assembled PCB photo
    Added photo of a fully assembled PCB.
2026-01-11 Add BOM and cable assembly instructions
    * Added signal cable assembly instructions.
    * Added BOM.
2026-01-11 Add software part description
    * Added description of a software part.
    * Minor README cleanups.
    * Added photo of a complete project.
    * Updated assembled top photo.
2026-01-11 Fix RTC init for DS12887
    Fix of the issue that for BQ3287MT the interrupts
    config was applied correctly, but for DS12887 it
    would not apply at all and the TSR didn't work.
    The problem was caused by lack of re-setting
    the index register after IN instruction.
